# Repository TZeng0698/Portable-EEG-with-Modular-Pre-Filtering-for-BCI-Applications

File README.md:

# Portable-EEG-with-Modular-Pre-Filtering-for-BCI-Applications
A Low-cost EEG BCI implementation with modular filtering card and ADS1298. The repo contains the PCB files and a guide to design your own

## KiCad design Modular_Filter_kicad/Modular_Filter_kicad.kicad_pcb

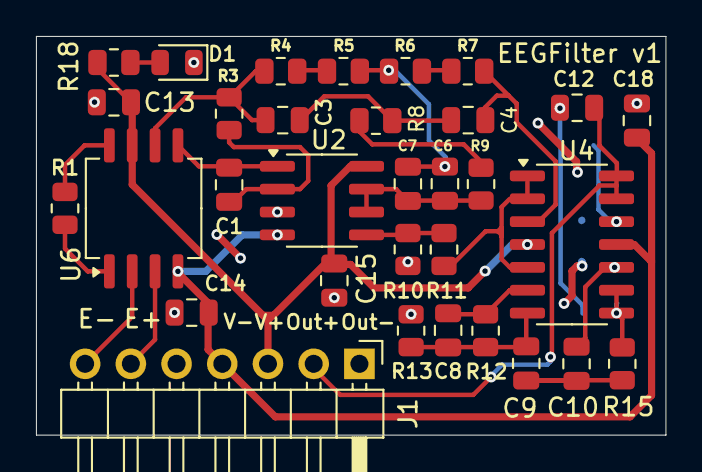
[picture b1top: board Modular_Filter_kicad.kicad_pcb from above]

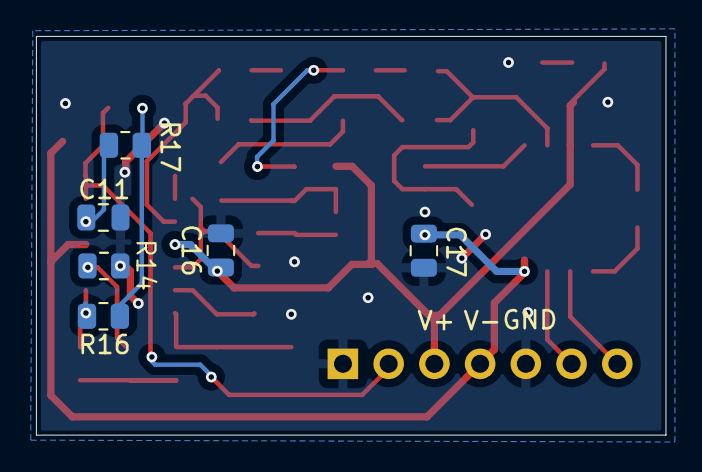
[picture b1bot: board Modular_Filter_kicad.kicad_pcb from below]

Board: 2 copper layers, 35.0 x 22.1 mm, 38 parts (6 on the bottom side), 28 nets.

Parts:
C1: 0.47u; C_0805_2012Metric
C3, C4, C6, C7: 10n; C_0805_2012Metric
C8: 33n; C_0805_2012Metric
C9, C10, C11, C12, C13, C16, C17, C18: 0.1u; C_0805_2012Metric
C14, C15: 1u; C_0805_2012Metric
D1: LED; LED_0805_2012Metric
J1: Conn_01x07_Pin; PinHeader_1x07_P2.54mm_Horizontal
R1: 20k; R_0805_2012Metric
R3: 3.3M; R_0805_2012Metric
R4, R6: 316k; R_0805_2012Metric
R5, R7, R13: 2k; R_0805_2012Metric
R8: 158k; R_0805_2012Metric
R9: 0.9k; R_0805_2012Metric
R10, R16, R17: 10k; R_0805_2012Metric
R11: 1k; R_0805_2012Metric
R12: 100k; R_0805_2012Metric
R14, R15: 4.7M; R_0805_2012Metric
R18: 5k; R_0805_2012Metric
U2: OPA2237; SOIC-8_3.9x4.9mm_P1.27mm
U4: OPA4170; SOIC-14_3.9x8.7mm_P1.27mm
U6: INA128; SOIC-8_5.3x6.2mm_P1.27mm

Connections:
/50Hz_Filtered_Out: R11.1, U4.1, U4.2 (-), U4.5 (+)
/50Hz_first_branch: C4.2, R7.1, U4.3 (+)
/50Hz_second_branch: C6.1, C7.1, R9.2, U2.6 (-), U2.7
/AC_COUPLER_OUT: C1.1, U2.1, U6.5 (Ref)
/E+: J1.6, U6.3 (+)
/E-: J1.7, U6.2 (-)
/E_OUT: C12.1, J1.2, U4.13 (-), U4.14
/First T: C6.2, C7.2, R5.1, R6.2
/HP_Out: R15.2, R16.1, U4.8, U4.9 (-)
/INA_OUT: C3.2, R3.2, R4.2, U6.6
/LP_1st_branch: C12.2, R16.2, R17.1
/MA_-Terminal: C8.1, R12.1, U4.6 (-)
/Main_Out: C8.2, C9.1, R12.2, R13.1, U4.7
/Second T: C3.1, C4.1, R8.1
AGND: C11.2, C13.1, C14.1, C15.1, C16.1, C17.1, C18.1, D1.1 (K), J1.1, J1.5, R10.2, R13.2, R14.2, U2.3 (+)
AVDD: C13.2, C15.2, C16.2, J1.3, R18.2, U2.8 (V+), U4.4 (V+), U6.7 (V+)
AVSS: C14.2, C17.2, C18.2, J1.4, U2.4 (V-), U4.11 (V-), U6.4 (V-)
unnamed: C9.2, C10.1, R15.1
unnamed: D1.2 (A), R18.1
unnamed: R1.1, U6.8 (Rg)
unnamed: R1.2, U6.1 (Rg)
unnamed: R4.1, R5.2
unnamed: R6.1, R7.2
unnamed: R8.2, R9.1
unnamed: C1.2, R3.1, U2.2 (-)
unnamed: R10.1, R11.2, U2.5 (+)
unnamed: C10.2, R14.1, U4.10 (+)
unnamed: C11.1, R17.2, U4.12 (+)

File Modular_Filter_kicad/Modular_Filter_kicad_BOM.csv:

Reference	Qty	Value	Footprint
C1	1	0.47u	Capacitor_SMD:C_0805_2012Metric
C3,C4,C9,C10,C11,C12,C13,C16,C17,C18	10	0.1u	Capacitor_SMD:C_0805_2012Metric
C6	1	0.22u	Capacitor_SMD:C_0805_2012Metric
C7	1	1pF	Capacitor_SMD:C_0805_2012Metric
C8	1	33n	Capacitor_SMD:C_0805_2012Metric
C14,C15	2	1u	Capacitor_SMD:C_0805_2012Metric
D1	1	LED	LED_SMD:LED_0805_2012Metric
J1	1	Conn_01x07_Pin	Connector_PinHeader_2.54mm:PinHeader_1x07_P2.54mm_Horizontal
R1	1	20k	Resistor_SMD:R_0805_2012Metric
R3	1	3.3M	Resistor_SMD:R_0805_2012Metric
R4,R6	2	30k	Resistor_SMD:R_0805_2012Metric
R5,R7	2	350	Resistor_SMD:R_0805_2012Metric
R8,R10,R16,R17	4	10k	Resistor_SMD:R_0805_2012Metric
R9	1	6.7k	Resistor_SMD:R_0805_2012Metric
R11	1	1k	Resistor_SMD:R_0805_2012Metric
R12	1	100k	Resistor_SMD:R_0805_2012Metric
R13	1	2k	Resistor_SMD:R_0805_2012Metric
R14,R15	2	4.7M	Resistor_SMD:R_0805_2012Metric
R18	1	5k	Resistor_SMD:R_0805_2012Metric
U2	1	OPA2237	Package_SO:SOIC-8_3.9x4.9mm_P1.27mm
U4	1	OPA4170	Package_SO:SOIC-14_3.9x8.7mm_P1.27mm
U6	1	INA128	Package_SO:SOIC-8_5.3x6.2mm_P1.27mm

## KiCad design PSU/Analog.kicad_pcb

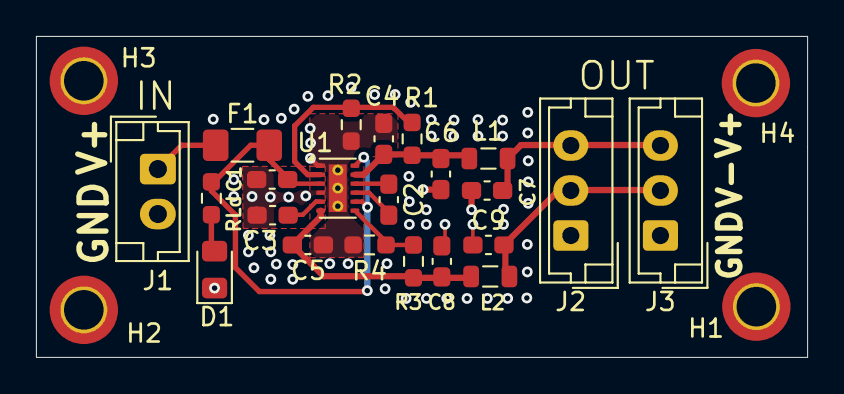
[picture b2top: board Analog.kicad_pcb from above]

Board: 2 copper layers, 42.8 x 17.8 mm, 26 parts (0 on the bottom side), 13 nets.

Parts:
C1, C3: 4.7u; C_0603_1608Metric_Pad1.08x0.95mm_HandSolder
C2: 0.47u; C_0603_1608Metric_Pad1.08x0.95mm_HandSolder
C4, C5: 2.2u; C_0603_1608Metric_Pad1.08x0.95mm_HandSolder
C6, C7, C8, C9: 10u; C_0603_1608Metric_Pad1.08x0.95mm_HandSolder
D1: LED; LED_0805_2012Metric_Pad1.15x1.40mm_HandSolder
F1: Fuse; Fuse_1206_3216Metric_Pad1.42x1.75mm_HandSolder
H1, H2, H3, H4: MountingHole_Pad; MountingHole_2.2mm_M2_DIN965_Pad_TopBottom
J1: Conn_01x02_Pin; JST_EH_B2B-EH-A_1x02_P2.50mm_Vertical
J2, J3: Conn_01x03_Pin; JST_EH_B3B-EH-A_1x03_P2.50mm_Vertical
L1, L2: 22u; L_0805_2012Metric
R1, R3: 110k; R_0603_1608Metric_Pad0.98x0.95mm_HandSolder
R2, R4: 100k; R_0603_1608Metric_Pad0.98x0.95mm_HandSolder
RLd: 5k; R_0603_1608Metric_Pad0.98x0.95mm_HandSolder
U1: LM27762; WSON-12-1EP_3x2mm_P0.5mm_EP1x2.65_ThermalVias

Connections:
/+2.52V: C4.2, C6.1, L1.1, R1.1, U1.11 (OUT+)
/-2.56V: C5.1, C8.1, L2.1, R3.2, U1.6 (OUT-)
/AVDD: C7.1, J2.3, J3.3, L1.2
/AVSS: C9.1, J2.2, J3.2, L2.2
/RAWA_Unprotected: F1.2, J1.1
AGND: C1.2, C3.2, C4.1, C5.2, C6.2, C7.2, C8.2, C9.2, D1.1 (K), H1.1, H2.1, H3.1, H4.1, J1.2, J2.1, J3.1, R2.2, R4.2, U1.1 (PGOOD), U1.4 (GND), U1.13 (PAD)
unnamed: D1.2 (A), RLd.2
unnamed: C2.1, U1.10 (C+)
unnamed: C2.2, U1.9 (C-)
unnamed: C3.1, U1.5 (CP)
unnamed: R1.2, R2.1, U1.2 (FB+)
unnamed: R3.1, R4.1, U1.7 (FB-)
RAW_A: C1.1, F1.1, RLd.1, U1.3 (VIN), U1.8 (EN-), U1.12 (EN+)

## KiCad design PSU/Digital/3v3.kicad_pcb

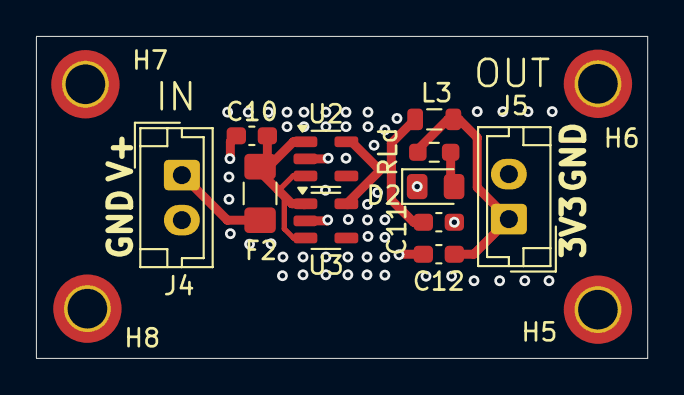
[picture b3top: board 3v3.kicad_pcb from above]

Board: 2 copper layers, 34.0 x 17.9 mm, 15 parts (0 on the bottom side), 6 nets.

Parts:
C10: 4.7u; C_0603_1608Metric_Pad1.08x0.95mm_HandSolder
C11, C12: 10u; C_0603_1608Metric_Pad1.08x0.95mm_HandSolder
D2: LED; LED_0805_2012Metric_Pad1.15x1.40mm_HandSolder
F2: Fuse; Fuse_1206_3216Metric_Pad1.42x1.75mm_HandSolder
H5, H6, H7, H8: MountingHole_Pad; MountingHole_2.2mm_M2_DIN965_Pad_TopBottom
J4, J5: Conn_01x02_Pin; JST_EH_B2B-EH-A_1x02_P2.50mm_Vertical
L3: 22u; L_0805_2012Metric
RLd: 5k; R_0603_1608Metric_Pad0.98x0.95mm_HandSolder
U2, U3: TLV70233_SOT23-5; SOT-23-5

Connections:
/3.3V: C12.1, J5.1, L3.2, RLd.1
/RAWD_Unprotected: F2.2, J4.1
DGND: C10.2, C11.2, C12.2, D2.1 (K), H5.1, H6.1, H7.1, H8.1, J4.2, J5.2, U2.2 (GND), U3.2 (GND)
unnamed: D2.2 (A), RLd.2
unnamed: C11.1, L3.1, U2.5 (OUT), U3.5 (OUT)
RAW_D: C10.1, F2.1, U2.1 (IN), U2.3 (EN), U3.1 (IN), U3.3 (EN)

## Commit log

2025-10-20 Add block diagram image to README
2025-10-20 Update image alt text in README
